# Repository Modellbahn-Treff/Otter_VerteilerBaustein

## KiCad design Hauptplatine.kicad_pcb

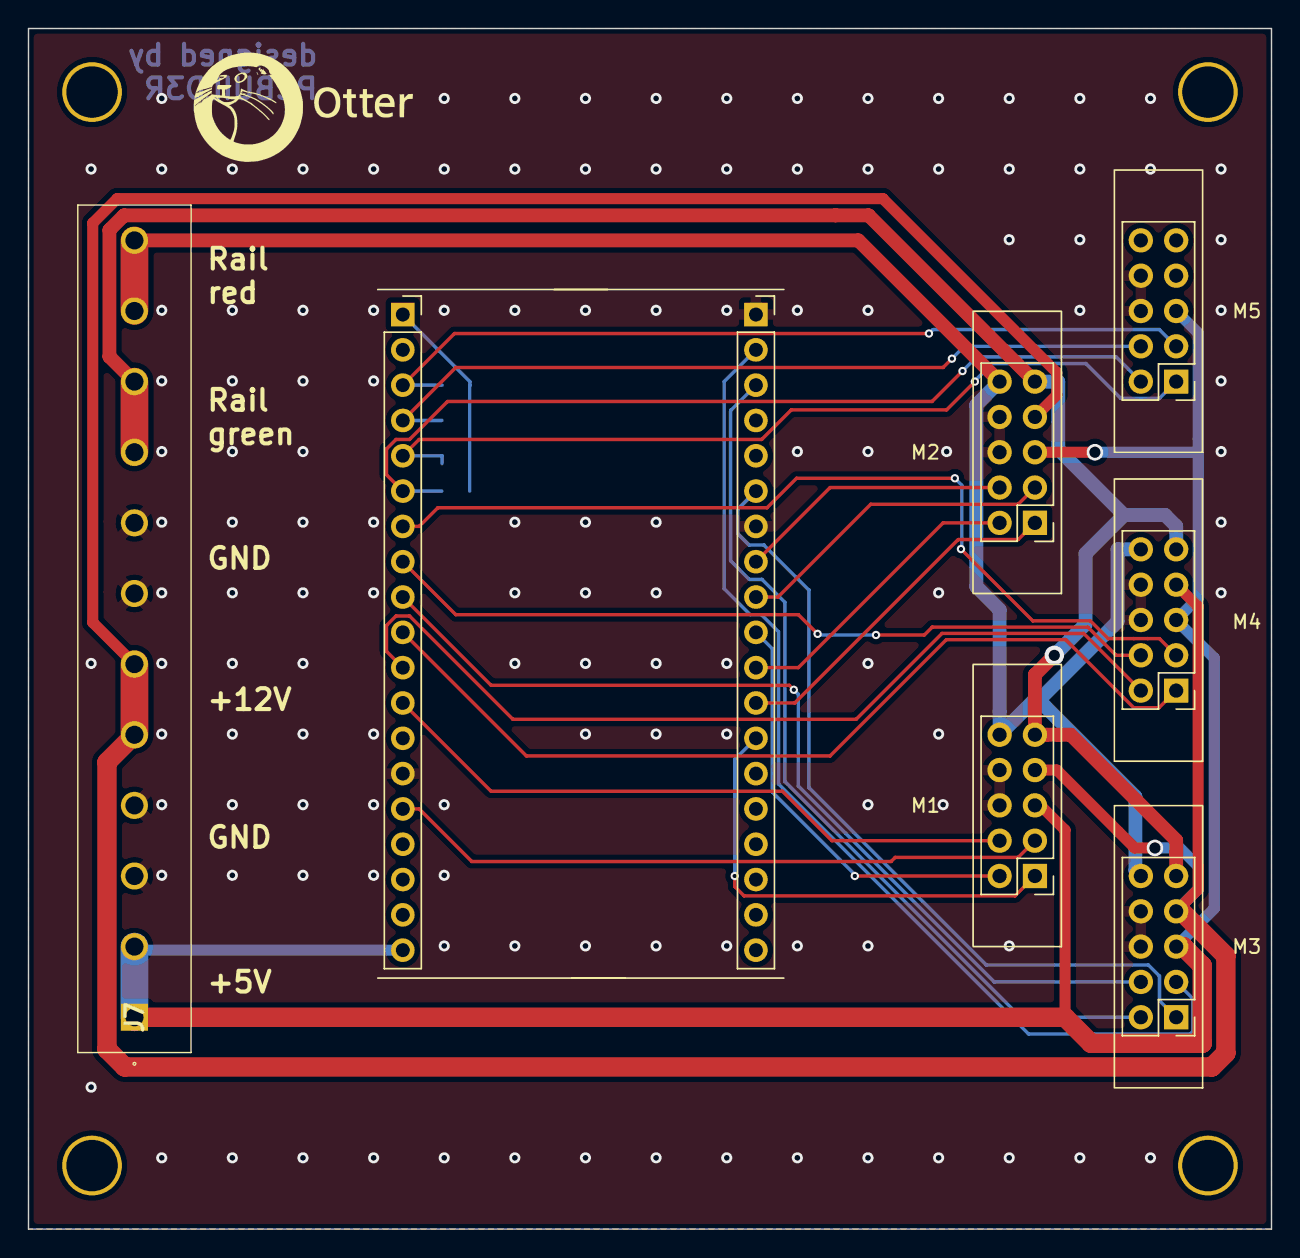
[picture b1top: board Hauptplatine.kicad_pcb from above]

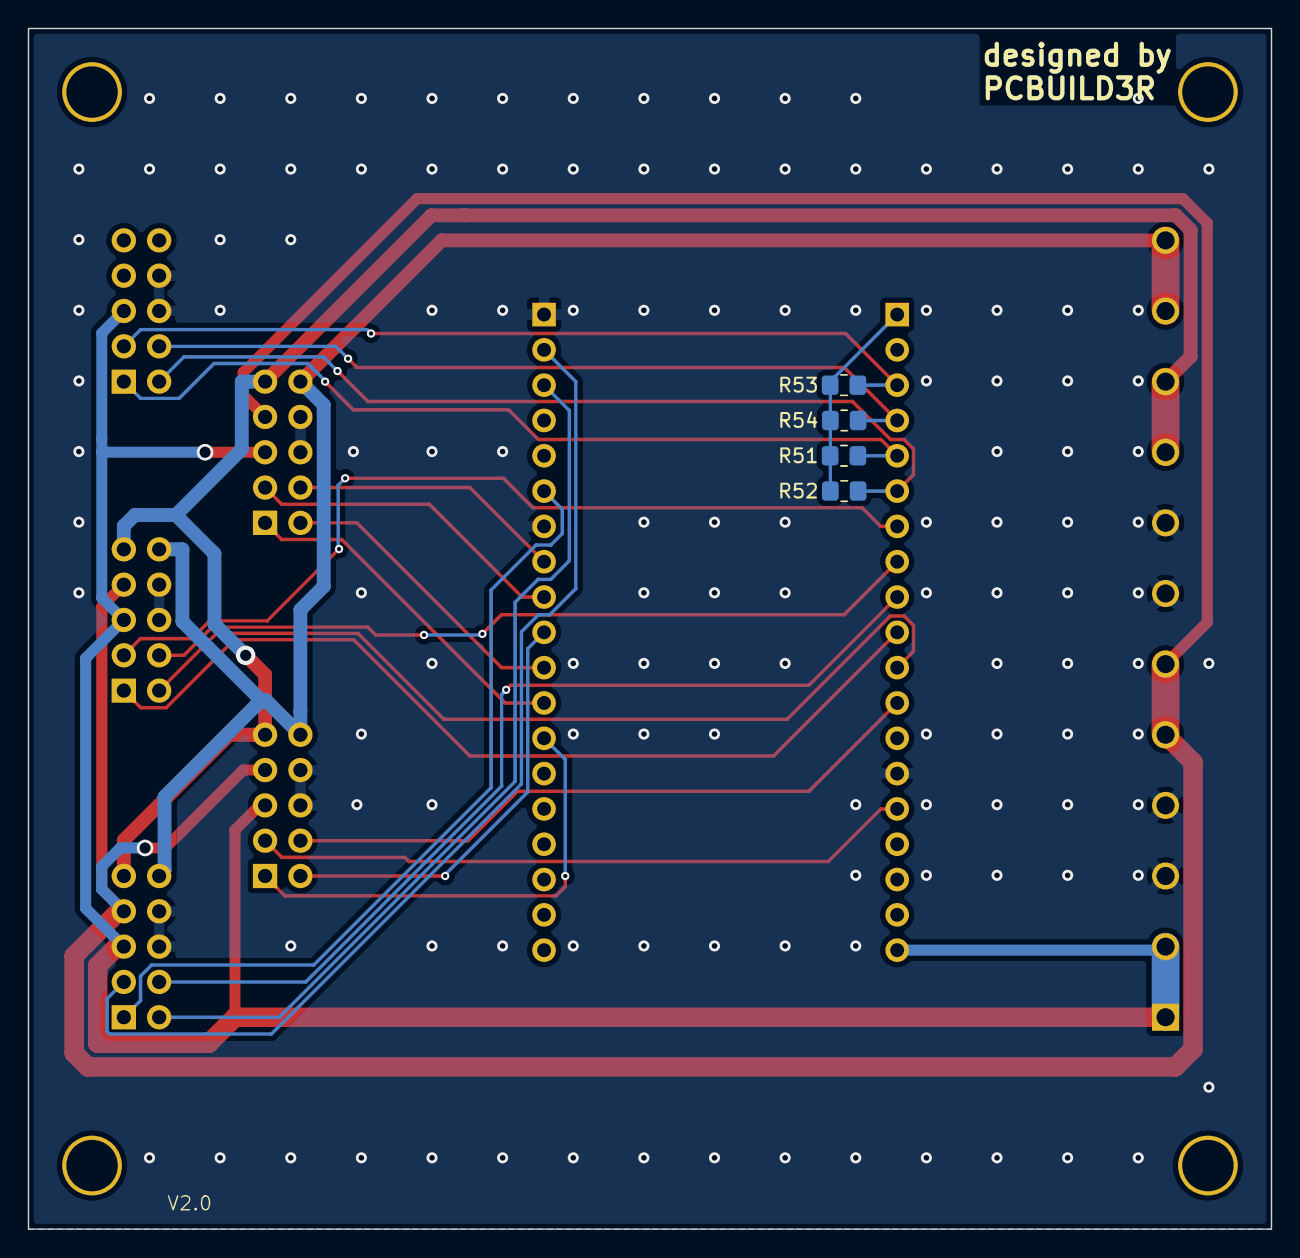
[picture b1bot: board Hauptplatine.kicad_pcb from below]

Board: 2 copper layers, 89.4 x 86.4 mm, 16 parts (4 on the bottom side), 26 nets.

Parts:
H1, H2, H3, H4: MountingHole; MountingHole_4.3mm_M4
J7: Conn_01x12_Female; 1729225
M1, M2, M3, M4, M5: Conn_01x10_Female; PinHeader_2x05_P2.54mm_Vertical_BKL
R51, R52, R53, R54: 10k; R_0805_2012Metric_Pad1.20x1.40mm_HandSolder
U2: esp32_dev4_left; esp32_dev_left
U3: esp32_dev4_right

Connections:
+3.3V: R51.1, R52.2, R53.2, R54.1, U2.1 (3.3V)
+5V: J7.1, J7.2, M1.5, M2.5, M3.5, M4.5, M5.5, U2.19 (5V)
+12V: J7.5, J7.6, M1.7, M2.7, M3.7, M4.7
+15V: J7.9, J7.10, M1.9, M2.9, M3.9, M4.9
-15V: J7.11, J7.12, M1.10, M2.10, M3.10, M4.10
GND: J7.3, J7.4, J7.7, J7.8, M1.6, M1.8, M2.6, M2.8, M3.6, M3.8, M4.6, M4.8, M5.6, M5.8, U2.14 (GND), U3.32 (GND), U3.38 (GND)
unnamed: M1.1, U3.26 (GPIO4)
unnamed: M1.2, U3.29 (GPIO5)
unnamed: M1.3, U2.15 (GPIO13)
unnamed: M1.4, U2.12 (GPIO14)
unnamed: M2.1, U3.27 (GPIO16)
unnamed: M2.2, U3.28 (GPIO17)
unnamed: M2.3, U3.30 (GPIO18)
unnamed: M2.4, U3.31 (GPIO19)
unnamed: M3.1, U3.33 (GPIO21)
unnamed: M3.2, U3.36 (GPIO22)
unnamed: M3.3, U3.37 (GPIO23)
unnamed: M3.4, U2.9 (GPIO25)
unnamed: M4.1, U2.10 (GPIO26)
unnamed: M4.2, U2.11 (GPIO27)
unnamed: M4.3, U2.7 (GPIO32)
unnamed: M4.4, U2.8 (GPIO33)
unnamed: M5.1, R51.2, U2.5 (GPI34)
unnamed: M5.2, R52.1, U2.6 (GPI35)
unnamed: M5.3, R53.1, U2.3 (GPI36)
unnamed: M5.4, R54.2, U2.4 (GPI39)

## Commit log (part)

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2026-05-03 Add .DS_Store to .gitignore
2026-05-05 final Design V2
2026-05-23 add firmware
2026-05-23 Update README.md for clarity and consistency in firmware documentation
2026-05-23 Add web interface and manifest for Otter VerteilerBaustein firmware flashing
    - Created index.html for the web interface, enabling users to flash firmware and configure WiFi settings directly from their browser.
    - Implemented a user-friendly layout with responsive design, including sections for flashing firmware and configuring WiFi credentials.
    - Added manifest.json to define the firmware build configuration for the ESP32 chip, specifying the necessary binary files and their offsets.
2026-05-23 Increase height of log display area in index.html for better visibility
2026-05-23 Enhance log display area in index.html for improved layout and readability
2026-05-23 Improve log handling by buffering incomplete lines in index.html
2026-05-23 Add log control buttons for console connection in index.html
2026-05-23 Refactor IP configuration section for improved layout and add live IP preview functionality
2026-05-25 Update initial states of TM_active, SM_active, and WM_active arrays for default behaviour
2026-05-25 Reduce main loop delay from 10 ms to 1 ms for improved responsiveness
2026-05-25 Update AusSchaltZeitWeiche to 200 for correct timing
2026-05-25 Update component requirements and refactor timing logic for WM module
2026-06-14 Add MQTT settings update functionality and improve JSON handling
2026-06-14 Increase MQTT buffer size to 2048 for improved data handling
2026-06-14 Add reboot functionality in settings_apply_json for MQTT requests
2026-06-14 Refactor settings handling to improve JSON parsing and NVS error reporting
2026-06-14 Fix MQTT ack never sent by using enqueue instead of publish
2026-06-14 Improve MQTT reboot handling by delaying restart in a separate task
2026-06-20 Refactor GitHub Actions workflow for improved deployment handling and versioning
2026-06-20 deploy: bf7afc85991025c8ca1795e6ca6e5c1c9b3d28cc
2026-06-20 Create CNAME
2026-06-20 deploy: e548e3d74f4be73f2a9a95022525069664152633
2026-06-20 Refactor deployment workflow to unify concurrency groups and enhance release deployment process
2026-06-20 deploy: b8569cc9c5007893c4d07d145cb7fcb6a441e84f
